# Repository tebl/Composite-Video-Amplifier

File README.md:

# Composite Video Amplifier

Based on schematic supplied by the user simon.plata over on [atariage.com](http://atariage.com/forums/topic/271678-simple-diy-composite-video-mod/), this module is intended for use when doing a composite modification of Atari consoles such as the Atari 2600. While not ideal, Composite for the most part is what we have available in the form of analog TV inputs where I live so if you haven't installed one already - I highly recommend that you try it since RF is truly horrible these days and your Atari deserves better!

I installed one of these in my PAL-region Atari 7800 and the results are very good, a significant improvement over the standard RF that originally comes as its only option. Granted, the 7800 is by no means the worst of the lot with the 2600 known to be particularly fuzzy. Just a few components to remove as well as adding the RCA-jacks, so all in all a good result for not too much work!

# Schematic
The supplied KiCad files should be sufficient as both a schematic and as a  starting point for ordering PCBs (basically you could just zip the contents of the export folder and upload that on a fabrication site), the schematic is also available in [PDF-format](https://github.com/tebl/Composite-Video-Amplifier/raw/master/export/Composite%20Video%20Amplifier.pdf) and this is what you'll need to print and work your way through this things don't work as expected after assembly.

# BOM
Most parts should be easy to get a hold of from your favourite local electronic component shop, but given that I don't have access to such shops where I live so everything was based on whatever I could get cheapest from ebay/AliExpress (free shipping, plan on usually waiting 3-4 weeks though). The list below should be everything you'll need in addition to a workable soldering iron and some 60/40 soldering tin. For superior results, consider using 1% accuracy resistors as well as shielded wire when doing the install!

| Reference    | Item                                  | Count |
| ------------ | ------------------------------------- | ----- |
| PCB          | Fabricate using Gerber files ([order](https://www.pcbway.com/project/shareproject/Atari_2600_Composite_Mod.html=88707))  |     1 |
| C1           | 47pf ceramic capacitor                |     1 |
| R1,R3        | 1k ohm resistor                       |     2 | 
| R2           | 3k3 (3300) ohm resistor               |     1 | 
| R4           | 150 ohm resistor                      |     1 | 
| R5           | 68 ohm resistor                       |     1 | 
| R6           | 18 ohm resistor                       |     1 | 
| R7           | 75 ohm resistor                       |     1 | 
| R8           | 10k ohm resistor                      |     1 | 
| RV1          | 3296W Potentiometer 5k Ohm            |     1 |
| Q1           | 2N3904 transistor (TO-92)             |     1 |
| Q2           | 2N3906 transistor (TO-92)             |     1 |

Please use the order link above when signing up to help me support this project, I'll get a small discount on future orders and hopefully that means I can afford to keep developing new and exciting modules in the future. By using the URL you won't have to deal with the rather daunting order forms for PCB fabrication, but if you want to go that route they'll probably want a zipped-up copy of the files in the export-directory!

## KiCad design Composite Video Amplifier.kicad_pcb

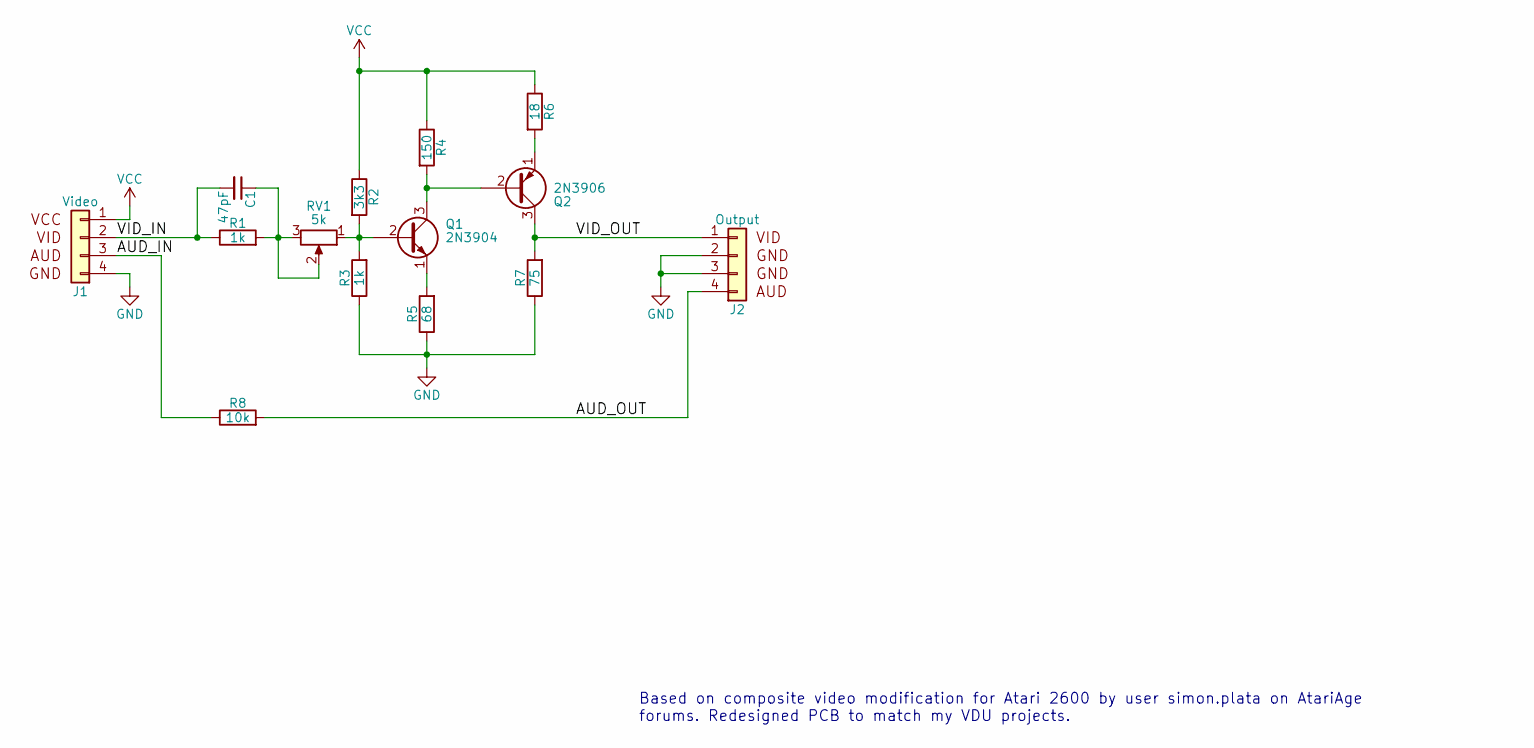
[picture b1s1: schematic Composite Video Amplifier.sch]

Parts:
C1: 47pF; C_Disc_D4.7mm_W2.5mm_P5.00mm
J1: Video; Pin_Header_Straight_1x04_Pitch2.54mm
J2: Output; Pin_Header_Straight_1x04_Pitch2.54mm
Q1: 2N3904; TO-92_Inline_Wide
Q2: 2N3906; TO-92_Inline_Wide
R1, R3: 1k; R_Axial_DIN0207_L6.3mm_D2.5mm_P10.16mm_Horizontal
R2: 3k3; R_Axial_DIN0207_L6.3mm_D2.5mm_P10.16mm_Horizontal
R4: 150; R_Axial_DIN0207_L6.3mm_D2.5mm_P10.16mm_Horizontal
R5: 68; R_Axial_DIN0207_L6.3mm_D2.5mm_P10.16mm_Horizontal
R6: 18; R_Axial_DIN0207_L6.3mm_D2.5mm_P10.16mm_Horizontal
R7: 75; R_Axial_DIN0207_L6.3mm_D2.5mm_P10.16mm_Horizontal
R8: 10k; R_Axial_DIN0207_L6.3mm_D2.5mm_P10.16mm_Horizontal
RV1: 5k; Potentiometer_Trimmer_Bourns_3296W

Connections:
/AUD_IN: J1.3 (Pin_2), R8.1
/AUD_OUT: J2.4 (Pin_1), R8.2
/VID_IN: C1.2, J1.2 (Pin_3), R1.1
/VID_OUT: J2.1 (Pin_4), Q2.3 (C), R7.2
GND: J1.4 (Pin_1), J2.2 (Pin_3), J2.3 (Pin_2), R3.1, R5.1, R7.1
unnamed: C1.1, R1.2, RV1.2, RV1.3
unnamed: Q1.1 (E), R5.2
unnamed: Q1.2 (B), R2.2, R3.2, RV1.1
unnamed: Q1.3 (C), Q2.2 (B), R4.2
unnamed: Q2.1 (E), R6.2
VCC: J1.1 (Pin_4), R2.1, R4.1, R6.1

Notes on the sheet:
Based on composite video modification for Atari 2600 by user simon.plata on AtariAge forums. Redesigned PCB to match my VDU projects.

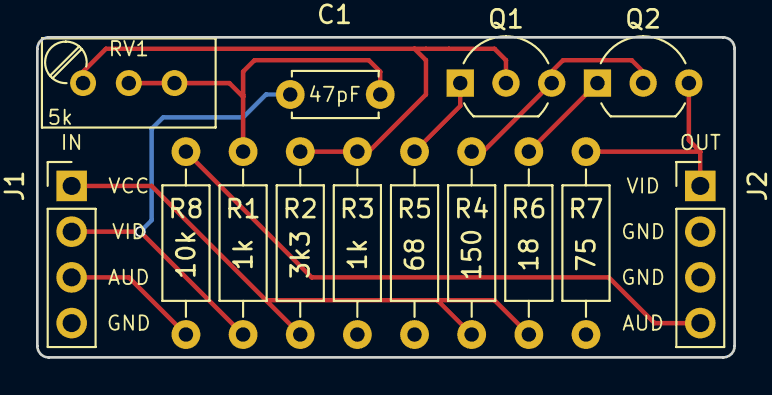
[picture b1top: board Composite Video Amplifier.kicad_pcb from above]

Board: 2 copper layers, 38.7 x 17.8 mm, 14 parts (0 on the bottom side), 11 nets.

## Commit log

2018-12-13 Added schematic and assigned footprints
2018-12-13 Fixed electrical checks
2018-12-13 PCB layout done
2018-12-13 Gerber export and simple README added.
2018-12-19 Ignore folder with temporary files
2019-02-14 Added resistor values to silkscreen
2019-02-28 Added gallery images
2019-02-28 Added pictures to README.
2021-02-01 Improved silkscreen markings
